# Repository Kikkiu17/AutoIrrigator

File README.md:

# Il progetto
Alla base del progetto c'è un microcontrollore **STM32G030F6P6**, compatto e dal costo di qualche decina di centesimi, che si interfaccia con un modulo **ESP-01S** per la connessione a Internet. Il microcontrollore può pilotare quattro elettrovalvole assieme a quattro sensori di flusso dell'acqua, uno per ogni tubo. I sensori di flusso permettono di rilevare la presenza di problemi lungo le linee e le quattro valvole consentono di irrigare fino a quattro aree alla volta.

Il tutto è **controllabile da remoto tramite un'app Android**, con la quale si possono aprire o chiudere le valvole manualmente ma si può anche impostare una programmazione per l'apertura e chiusura automatica in base all'orario o al tempo atmosferico. Infatti, il microcontrollore effettua ogni 15 minuti una richiesta all'API Open-Meteo per **ottenere le previsioni meteo della giornata**: se è prevista pioggia, è inutile irrigare, quindi le valvole resteranno chiuse.
# Costruzione
## Hardware
### Circuito stampato
Ho iniziato con l'hardware. Ho sviluppato un circuito elettronico in KiCad in modo che l'STM potesse controllare le valvole e i sensori. Le valvole sono a 12 V e consumano ~600 mA di corrente, quindi ho usato MOSFET AO3400A per poterle controllare con l'STM (i cui pin hanno un output massimo di ~15 mA a 3,3 V). Pure i sensori di flusso operano a 12 V, quindi ho usato gli stessi MOSFET per poterli interfacciare col microcontrollore.

Ho poi stampato in 3D uno stencil per poter spalmare la pasta saldante sui vari pad dei componenti a montaggio superficiale (SMD). Questo perché ordinarlo assieme alle PCB sarebbe costato quasi 20 € in più, mentre così è gratis e il risultato è comunque accettabile. Quindi perché no?

Schema:

PCB:

Stencil fatto in casa

### Modello 3D
Mentre aspettavo l'arrivo delle PCB, ho iniziato a creare il modello 3D del progetto, con dei raccordi per le valvole e i sensori. Ho creato un design abbastanza compatto ma comunque semplice da assemblare, con il circuito stampato al centro in modo da poterci collegare tutti i fili comodamente.

## Software
### Firmware embedded
Dopo aver fatto i raccordi e i supporti, sono passato al software. Ho iniziato a scrivere il [mio driver](https://github.com/Kikkiu17/ESP-AT-STM32) per l'ESP-01S dato che non ne ho trovato nessuno online abbastanza semplice da usare compatibile con l'STM32. Il driver sfrutta il DMA dell'STM32 per poter ricevere i dati dell'ESP dalla porta seriale senza usare la CPU, aumentando quindi le prestazioni (in questo caso le prestazioni non sono critiche, ma fa comunque comodo). L'ESP viene connesso alla rete WiFi; viene impostato l'hostname `ESPDEVICE002` per poter essere riconosciuto nella rete; viene impostato il nome `Hub irrigazione`; viene connesso al server NTP in modo da poter ottenere la data e l'ora e infine l'ESP viene impostato in modalità `server` in modo da accettare connessioni remote sulla porta `23`. Poi, nel ciclo while principale, il firmware attende nuove richieste tramite la funzione `WIFI_ReceiveRequest` che dopo verranno gestite.

Grazie ai numerosi timer dell'STM32G030F6P6, ho dedicato tre timer ai quattro sensori di flusso (chiamati FLOW): TIM14 per FLOW1, TIM1 per FLOW2, TIM3 per FLOW3 e FLOW4. In questo modo ho potuto usare quattro pin fisici per ciascun sensore, invece che fare multiplexing coi quattro sensori, rendendo quindi tutto molto più semplice. Imposto i canali timer dei sensori in modalità `Input compare` e abilito gli interrupt per i timer, in modo da ottenere il periodo del segnale PWM dei sensori. Facendo `1/T`, dove T è il periodo, si ottiene la frequenza e dividendola per 7,5 si ottiene il flusso d'acqua in `litri/min`.

Infine ho scritto del codice per connettermi all'API di Open-meteo per ottenere le [previsioni per il giorno corrente](http://api.open-meteo.com/v1/forecast?latitude=45.5582&longitude=9.2149&hourly=precipitation,precipitation_probability&current=precipitation&timezone=auto&forecast_days=1) tramite la funzione `WEATHER_GetForecast`. Le previsioni vengono immagazzinate in degli array in modo da poter accedere facilmente ad esse.

### App Android

Per controllare il tutto si usa un'app Android, ESPValve. Volevo utilizzare l'app [ESPIOT](https://github.com/Kikkiu17/espiot) di un mio vecchio progetto, ma il modo in cui l'ho scritta rende difficile l'integrazione di nuovi dispositivi ad essa, quindi ho deciso di riscriverla da zero. La vecchia app richiedeva delle caratteristiche specifiche da chiedere ai dispositivi connessi, quindi per aggiungere, ad esempio, un pulsante, bisognava modificare in modo pesante sia l'applicazione che il dispositivo (in questo caso l'STM32 e l'ESP). La nuova app invece chiede ogni 250 ms un pacchetto di `feature` dal dispositivo con questa struttura: `tipoX$Nome,caratteristica_aggiuntiva$Nome$dato` oppure `tipoX$Nome$dato`. `tipo` è il tipo di caratteristica, quindi interruttore, bottone, sensore o timestamp e `caratteristica_aggiuntiva` può essere ad esempio `sensore`. In questo modo, posso creare il pacchetto di caratteristiche che mi interessano e l'app Android crea ogni bottone o sensore o altro col nome specificato e col dato specificato, in base alla struttura data.

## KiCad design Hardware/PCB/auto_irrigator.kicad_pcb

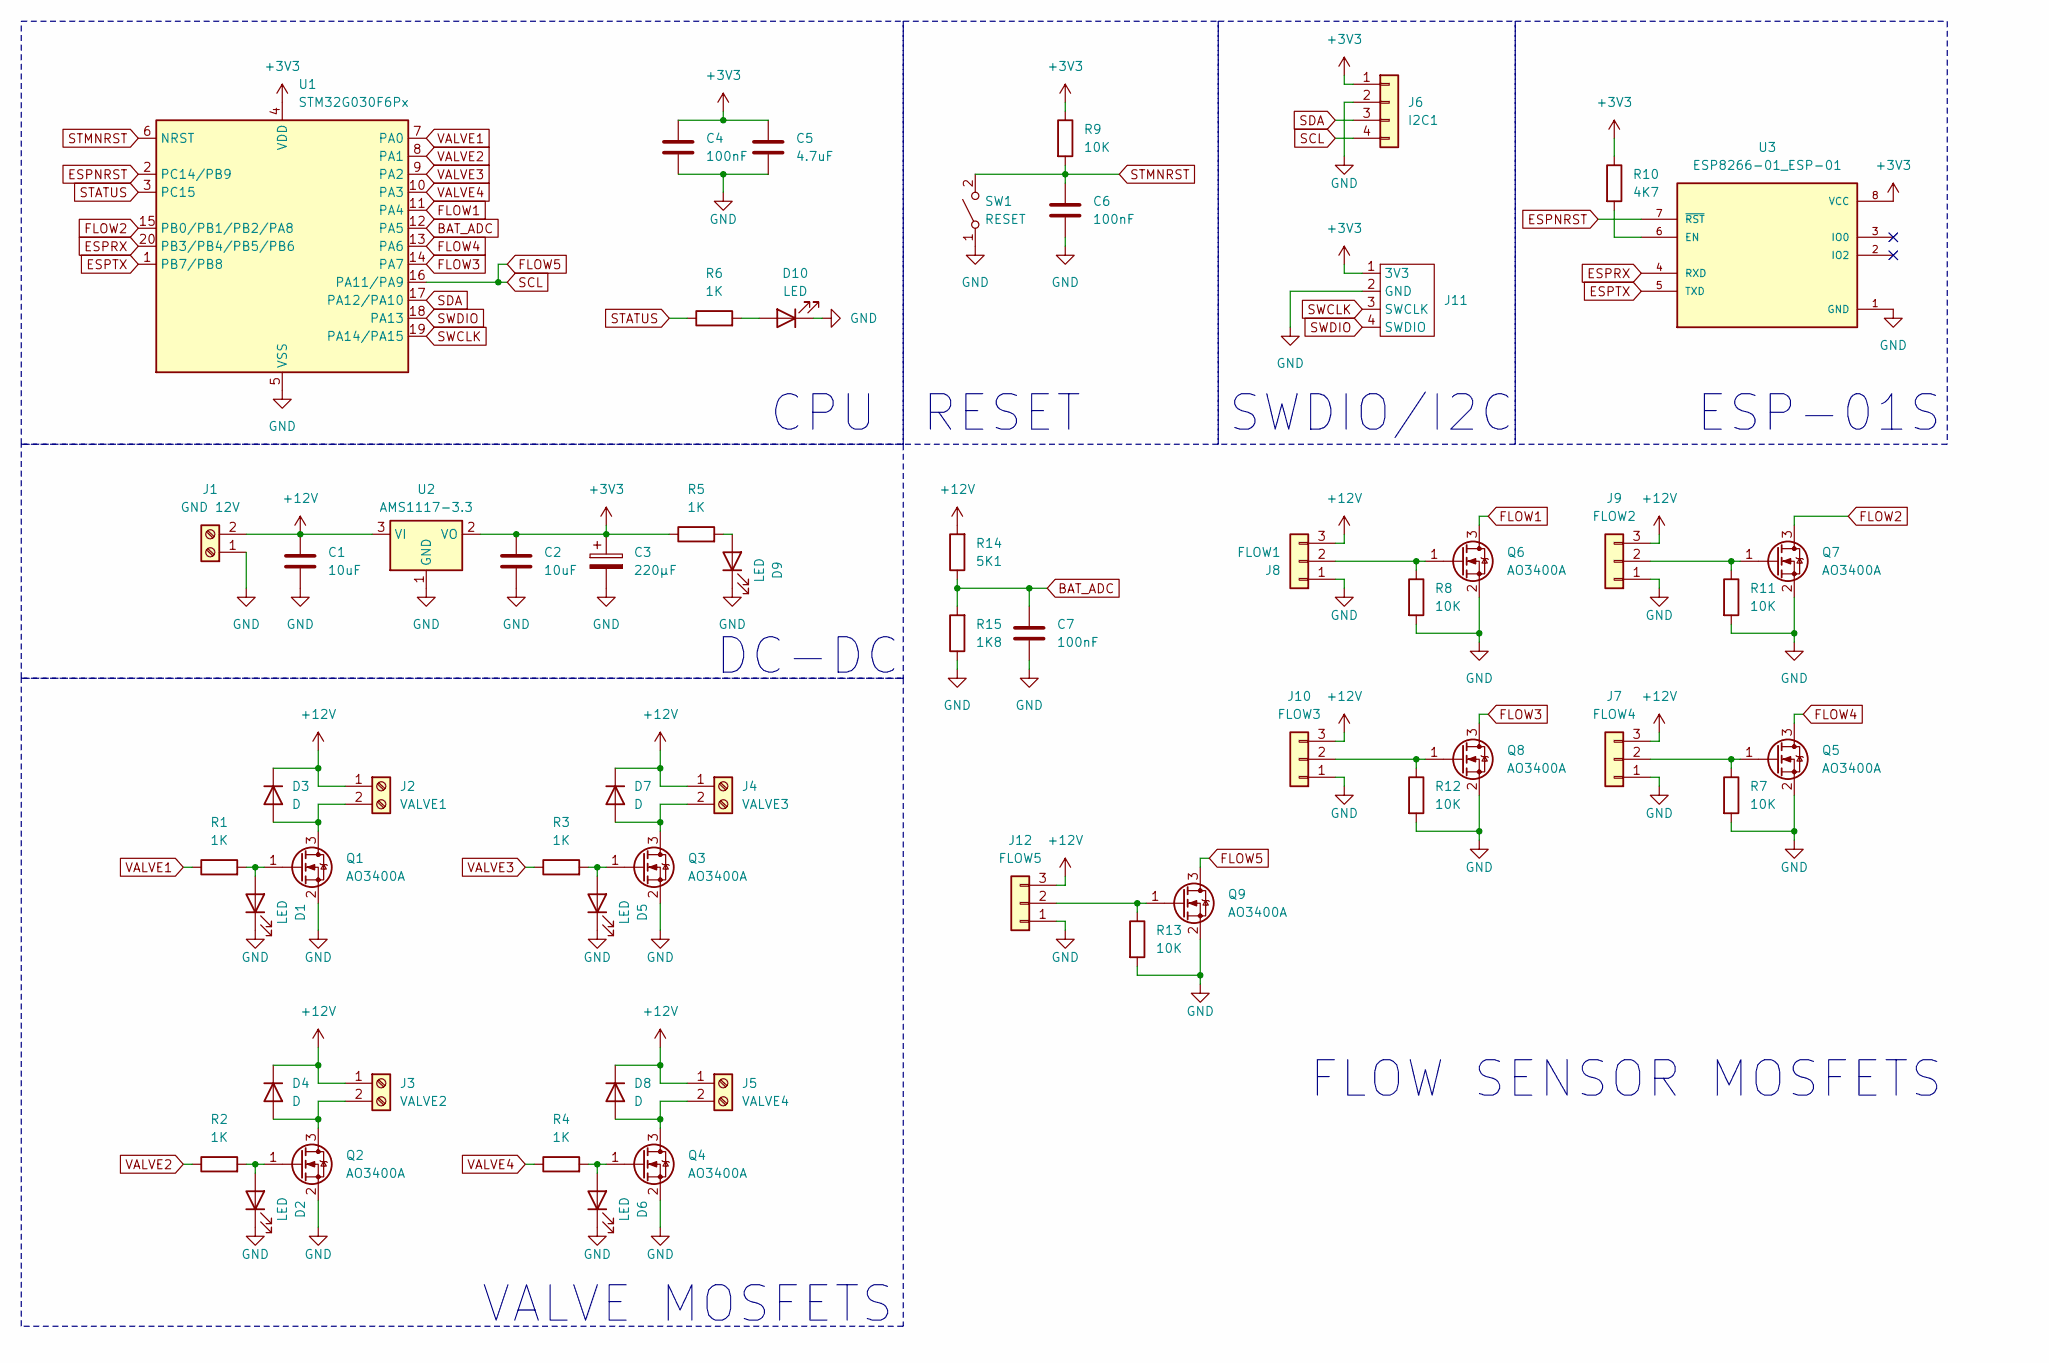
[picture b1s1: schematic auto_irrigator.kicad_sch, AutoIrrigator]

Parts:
C1, C2: 10uF; C_0603_1608Metric
C3: 220µF; CP_Radial_D4.0mm_P1.50mm
C4, C6, C7: 100nF; C_0603_1608Metric
C5: 4.7uF; C_0603_1608Metric
D1, D2, D5, D6, D9: LED; LED_0603_1608Metric
D3, D4, D7, D8: D; D_SMA
D10: LED; LED_0805_2012Metric
J1: GND 12V; screw_2p_small
J2: VALVE1; screw_2p_small
J3: VALVE2; screw_2p_small
J4: VALVE3; screw_2p_small
J5: VALVE4; screw_2p_small
J6: I2C1; JST_EH_B4B-EH-A_1x04_P2.50mm_Vertical
J7: FLOW4; JST_EH_B3B-EH-A_1x03_P2.50mm_Vertical
J8: FLOW1; JST_EH_B3B-EH-A_1x03_P2.50mm_Vertical
J9: FLOW2; JST_EH_B3B-EH-A_1x03_P2.50mm_Vertical
J10: FLOW3; JST_EH_B3B-EH-A_1x03_P2.50mm_Vertical
J11: swdio
J12: FLOW5; JST_EH_B3B-EH-A_1x03_P2.50mm_Vertical
Q1, Q2, Q3, Q4, Q5, Q6, Q7, Q8, Q9: AO3400A; SOT-23
R1, R2, R3, R4, R5, R6: 1K; R_0603_1608Metric
R7, R8, R9, R11, R12, R13: 10K; R_0603_1608Metric
R10: 4K7; R_0603_1608Metric
R14: 5K1; R_0603_1608Metric
R15: 1K8; R_0603_1608Metric
SW1: RESET; SW_PUSH_6mm
U1: STM32G030F6Px; TSSOP-20_4.4x6.5mm_P0.65mm
U2: AMS1117-3.3; SOT-223-3_TabPin2
U3: ESP8266-01_ESP-01; esp-01s; PARTREV V1.2

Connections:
+3V3: C2.1, C3.1, C4.1, C5.1, J6.1, J11.1 (3V3), R5.1, R9.1, R10.1, U1.4 (VDD), U2.2 (VO), U3.8 (VCC)
+12V: C1.1, D3.1 (K), D4.1 (K), D7.1 (K), D8.1 (K), J1.2, J2.1, J3.1, J4.1, J5.1, J7.3, J8.3, J9.3, J10.3, J12.3, R14.2, U2.3 (VI)
BAT_ADC: C7.1, R14.1, R15.2, U1.12 (PA5)
ESPNRST: U1.2 (PC14/PB9), U3.7 (~RST)
ESPRX: U1.20 (PB3/PB4/PB5/PB6), U3.4 (RXD)
ESPTX: U1.1 (PB7/PB8), U3.5 (TXD)
FLOW1: Q6.3 (D), U1.11 (PA4)
FLOW2: Q7.3 (D), U1.15 (PB0/PB1/PB2/PA8)
FLOW3: Q8.3 (D), U1.14 (PA7)
FLOW4: Q5.3 (D), U1.13 (PA6)
FLOW5: J6.4, Q9.3 (D), U1.16 (PA11/PA9)
GND: C1.2, C2.2, C3.2, C4.2, C5.2, C6.2, C7.2, D1.1 (K), D2.1 (K), D5.1 (K), D6.1 (K), D9.1 (K), D10.1 (K), J1.1, J6.2, J7.1, J8.1, J9.1, J10.1, J11.2 (GND), J12.1, Q1.2 (S), Q2.2 (S), Q3.2 (S), Q4.2 (S), Q5.2 (S), Q6.2 (S), Q7.2 (S), Q8.2 (S), Q9.2 (S), R7.2, R8.2, R11.2, R12.2, R13.2, R15.1, SW1.1 (A), U1.5 (VSS), U2.1 (GND), U3.1 (GND)
unnamed: D1.2 (A), Q1.1 (G), R1.2
unnamed: D2.2 (A), Q2.1 (G), R2.2
unnamed: D3.2 (A), J2.2, Q1.3 (D)
unnamed: D4.2 (A), J3.2, Q2.3 (D)
unnamed: D5.2 (A), Q3.1 (G), R3.2
unnamed: D6.2 (A), Q4.1 (G), R4.2
unnamed: D7.2 (A), J4.2, Q3.3 (D)
unnamed: D8.2 (A), J5.2, Q4.3 (D)
unnamed: D9.2 (A), R5.2
unnamed: D10.2 (A), R6.2
unnamed: J7.2, Q5.1 (G), R7.1
unnamed: J8.2, Q6.1 (G), R8.1
unnamed: J9.2, Q7.1 (G), R11.1
unnamed: J10.2, Q8.1 (G), R12.1
unnamed: J12.2, Q9.1 (G), R13.1
unnamed: R10.2, U3.6 (EN)
SDA: J6.3, U1.17 (PA12/PA10)
STATUS: R6.1, U1.3 (PC15)
STMNRST: C6.1, R9.2, SW1.2 (B), U1.6 (NRST)
SWCLK: J11.3 (SWCLK), U1.19 (PA14/PA15)
SWDIO: J11.4 (SWDIO), U1.18 (PA13)
VALVE1: R1.1, U1.7 (PA0)
VALVE2: R2.1, U1.8 (PA1)
VALVE3: R3.1, U1.9 (PA2)
VALVE4: R4.1, U1.10 (PA3)

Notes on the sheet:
RESET
CPU
SWDIO/I2C
VALVE MOSFETS
DC-DC
ESP-01S
FLOW SENSOR MOSFETS

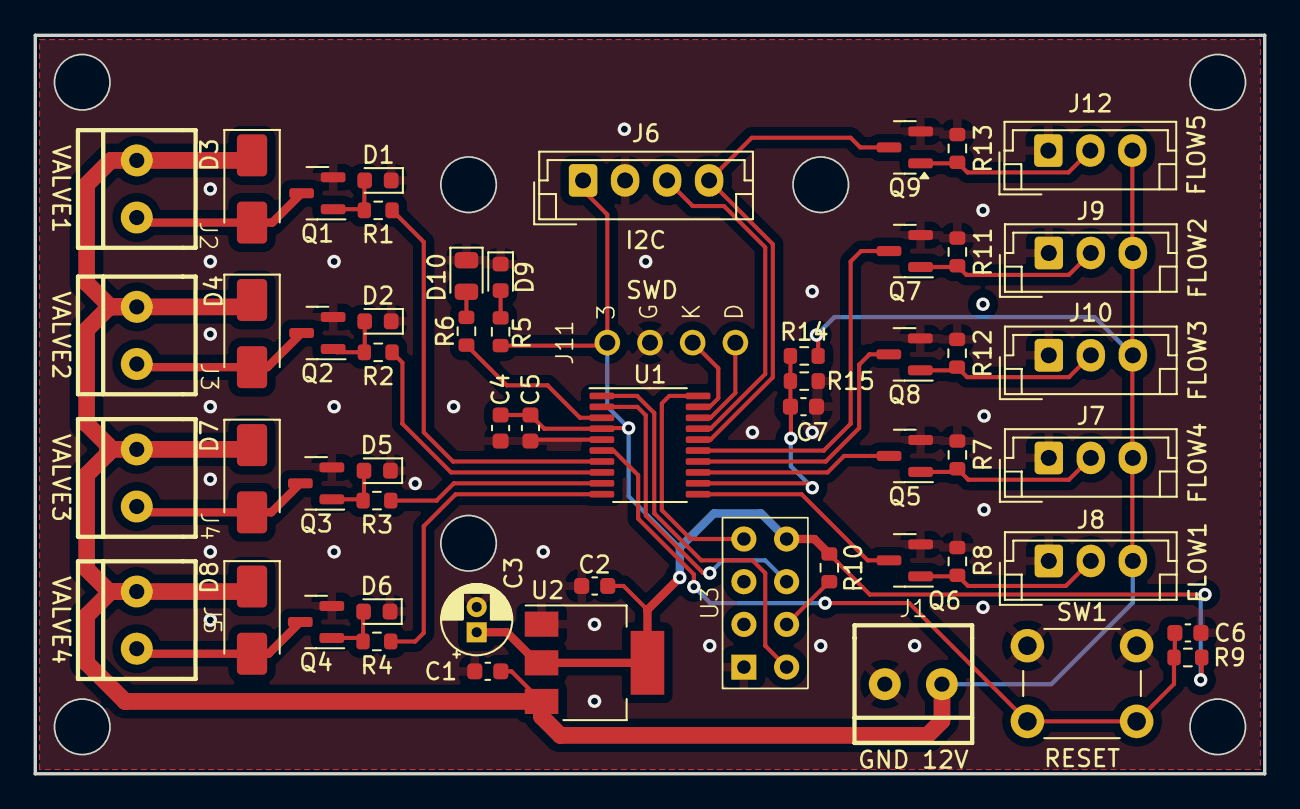
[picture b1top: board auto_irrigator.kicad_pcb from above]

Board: 2 copper layers, 73.2 x 43.9 mm, 57 parts (0 on the bottom side), 37 nets.

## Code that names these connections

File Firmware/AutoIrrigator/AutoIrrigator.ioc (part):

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Mcu.Name=STM32G030F6Px
Mcu.Package=TSSOP20
Mcu.UserName=STM32G030F6Px
PA0.GPIOParameters=PinState,GPIO_PuPd,GPIO_Label
PA0.GPIO_Label=VALVE1
PA0.GPIO_PuPd=GPIO_NOPULL
PA0.PinState=GPIO_PIN_RESET
PA0.Signal=GPIO_Output
PA1.GPIOParameters=GPIO_PuPd,GPIO_Label
PA1.GPIO_Label=VALVE2
PA1.GPIO_PuPd=GPIO_NOPULL
PA1.Signal=GPIO_Output
PA11\ [PA9].Signal=S_TIM1_CH4
PA13.Mode=Serial_Wire
PA13.Signal=SYS_SWDIO
PA14-BOOT0.Mode=Serial_Wire
PA14-BOOT0.Signal=SYS_SWCLK
PA14-BOOT0__PA15.StandardMode=true
PA2.GPIOParameters=GPIO_PuPd,GPIO_Label
PA2.GPIO_Label=VALVE3
PA2.GPIO_PuPd=GPIO_NOPULL
PA2.Signal=GPIO_Output
PA3.GPIOParameters=GPIO_PuPd,GPIO_Label
PA3.GPIO_Label=VALVE4
PA3.GPIO_PuPd=GPIO_NOPULL
PA3.Signal=GPIO_Output
PA4.GPIOParameters=GPIO_PuPd,GPIO_Label
PA4.GPIO_Label=FLOW1
PA4.GPIO_PuPd=GPIO_PULLUP
PA4.Signal=S_TIM14_CH1
PA5.GPIOParameters=GPIO_Label
PA5.GPIO_Label=BAT
PA5.Mode=IN5
PA5.Signal=ADC1_IN5
PA6.GPIOParameters=GPIO_PuPd,GPIO_Label
PA6.GPIO_Label=FLOW4
PA6.GPIO_PuPd=GPIO_PULLUP
PA6.Signal=S_TIM3_CH1
PA7.GPIOParameters=GPIO_PuPd,GPIO_Label
PA7.GPIO_Label=FLOW3
PA7.GPIO_PuPd=GPIO_PULLUP
PA7.Signal=S_TIM3_CH2
PB0__PB1__PB2__PA8.StandardMode=true
PB1.GPIOParameters=GPIO_Label
PB1.GPIO_Label=FLOW2
PB1.Signal=S_TIM3_CH4
PB3__PB4__PB5__PB6.StandardMode=true
PB6.GPIOParameters=GPIO_PuPd
PB6.GPIO_PuPd=GPIO_PULLUP
PB6.Mode=Asynchronous
PB6.Signal=USART1_TX
PB7.GPIOParameters=GPIO_PuPd
PB7.GPIO_PuPd=GPIO_PULLUP
PB7.Mode=Asynchronous
PB7.Signal=USART1_RX
PB7__PB8.StandardMode=true
PB9.GPIOParameters=PinState,GPIO_PuPd,GPIO_Label
PB9.GPIO_Label=ESPRST
PB9.GPIO_PuPd=GPIO_NOPULL
PB9.PinState=GPIO_PIN_SET
PB9.Signal=GPIO_Output
PC14-OSC32_IN\ (PC14)__PB9.StandardMode=true
PC15-OSC32_OUT\ (PC15).GPIOParameters=GPIO_Label
PC15-OSC32_OUT\ (PC15).GPIO_Label=STATUS
PC15-OSC32_OUT\ (PC15).Signal=GPIO_Output
RCC.HSE_VALUE=8000000
RCC.SYSCLKFreq_VALUE=64000000
RCC.SYSCLKSource=RCC_SYSCLKSOURCE_PLLCLK
board=custom

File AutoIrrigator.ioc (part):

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Mcu.Name=STM32G030F6Px
Mcu.Package=TSSOP20
Mcu.UserName=STM32G030F6Px
PA0.GPIOParameters=GPIO_PuPd,GPIO_Label
PA0.GPIO_Label=VALVE1
PA0.GPIO_PuPd=GPIO_NOPULL
PA0.Signal=GPIO_Output
PA1.GPIOParameters=GPIO_PuPd,GPIO_Label
PA1.GPIO_Label=VALVE2
PA1.GPIO_PuPd=GPIO_NOPULL
PA1.Signal=GPIO_Output
PA11\ [PA9].Mode=I2C
PA11\ [PA9].Signal=I2C2_SCL
PA12\ [PA10].Mode=I2C
PA12\ [PA10].Signal=I2C2_SDA
PA13.Mode=Serial_Wire
PA13.Signal=SYS_SWDIO
PA14-BOOT0.Mode=Serial_Wire
PA14-BOOT0.Signal=SYS_SWCLK
PA14-BOOT0__PA15.StandardMode=true
PA2.GPIOParameters=GPIO_PuPd,GPIO_Label
PA2.GPIO_Label=VALVE3
PA2.GPIO_PuPd=GPIO_NOPULL
PA2.Signal=GPIO_Output
PA3.GPIOParameters=GPIO_PuPd,GPIO_Label
PA3.GPIO_Label=VALVE4
PA3.GPIO_PuPd=GPIO_NOPULL
PA3.Signal=GPIO_Output
PA4.GPIOParameters=GPIO_PuPd,GPIO_Label
PA4.GPIO_Label=FLOW1
PA4.GPIO_PuPd=GPIO_PULLUP
PA4.Signal=S_TIM14_CH1
PA6.GPIOParameters=GPIO_PuPd,GPIO_Label
PA6.GPIO_Label=FLOW4
PA6.GPIO_PuPd=GPIO_PULLUP
PA6.Signal=S_TIM3_CH1
PA7.GPIOParameters=GPIO_PuPd,GPIO_Label
PA7.GPIO_Label=FLOW3
PA7.GPIO_PuPd=GPIO_PULLUP
PA7.Signal=S_TIM3_CH2
PA8.GPIOParameters=GPIO_PuPd,GPIO_Label
PA8.GPIO_Label=FLOW2
PA8.GPIO_PuPd=GPIO_PULLUP
PA8.Signal=S_TIM1_CH1
PB0__PB1__PB2__PA8.StandardMode=true
PB3__PB4__PB5__PB6.StandardMode=true
PB6.Mode=Asynchronous
PB6.Signal=USART1_TX
PB7.Mode=Asynchronous
PB7.Signal=USART1_RX
PB7__PB8.StandardMode=true
PB9.GPIOParameters=PinState,GPIO_PuPd,GPIO_Label
PB9.GPIO_Label=ESPRST
PB9.GPIO_PuPd=GPIO_NOPULL
PB9.PinState=GPIO_PIN_SET
PB9.Signal=GPIO_Output
PC14-OSC32_IN\ (PC14)__PB9.StandardMode=true
PC15-OSC32_OUT\ (PC15).GPIOParameters=GPIO_Label
PC15-OSC32_OUT\ (PC15).GPIO_Label=STATUS
PC15-OSC32_OUT\ (PC15).Signal=GPIO_Output
RCC.HSE_VALUE=8000000
RCC.SYSCLKFreq_VALUE=64000000
RCC.SYSCLKSource=RCC_SYSCLKSOURCE_PLLCLK
board=custom

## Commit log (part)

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2025-04-08 Caricamento iniziale
2025-04-08 Gestione comandi valvole
2025-04-12 Aggiunti gestori richieste
2025-04-13 Aggiunta ricerca key e value
2025-04-26 Aggiunta funzioni
    Aggiunte funzioni WEATHER per ottenere le previsioni meteo per la giornata attuale e funzione FLOW per il calcolo del flusso d'acqua
2025-04-26 Aggiunta immagini
2025-04-26 Aggiunta PCB, 3D, App Android
2025-05-15 Timer programmabile
2025-05-19 Programmazione apertura/chiusura
2025-08-08 Bugfix render pagina & disconnessione
    Sistemato bug per cui la pagina del dispositivo rimaneva vuota cambiando menù. Sistemato bug per cui quando l'app andava in sospensione in background non si riconnetteva più al dispositivo.
2025-08-09 Aggiunta programmazione e salvataggio su flash
    La programmazione dell'apertura e chiusura delle valvole adesso viene salvata sulla memoria FLASH del microcontrollore. Sarà possibile salvare anche altri elementi in futuro grazie alla nuova struttu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
2025-08-09 Aggiunta modalità scura e impostazioni
2025-08-09 Salva su FLASH anche il nome
2025-08-11 Migliorata stabilità
2025-08-21 AutoIrrigator rev 2
    Aggiunte notifiche. Migliorata ulteriormente la stabilità. Modificata PCB per sistemare gli errori della rev 1.
2025-08-25 Rimosso il BOM
2025-09-09 Aggiornato driver ESP (stabilità)
2025-09-09 Driver ESP (semplificato)
2025-09-28 Aggiornato driver ESP-AT
2025-09-28 Rimosso file inutilizzato
2025-10-03 Fixed write past the end of array
2025-10-03 Fixed name reading issue
2025-10-22 Improved safety
2026-02-05 Updated AT firmware
2026-02-05 Updated ESP AT firmware
2026-03-01 Updated ESP-AT firmware
2026-05-02 Updated ESP driver
2026-05-04 Changed folder structure
